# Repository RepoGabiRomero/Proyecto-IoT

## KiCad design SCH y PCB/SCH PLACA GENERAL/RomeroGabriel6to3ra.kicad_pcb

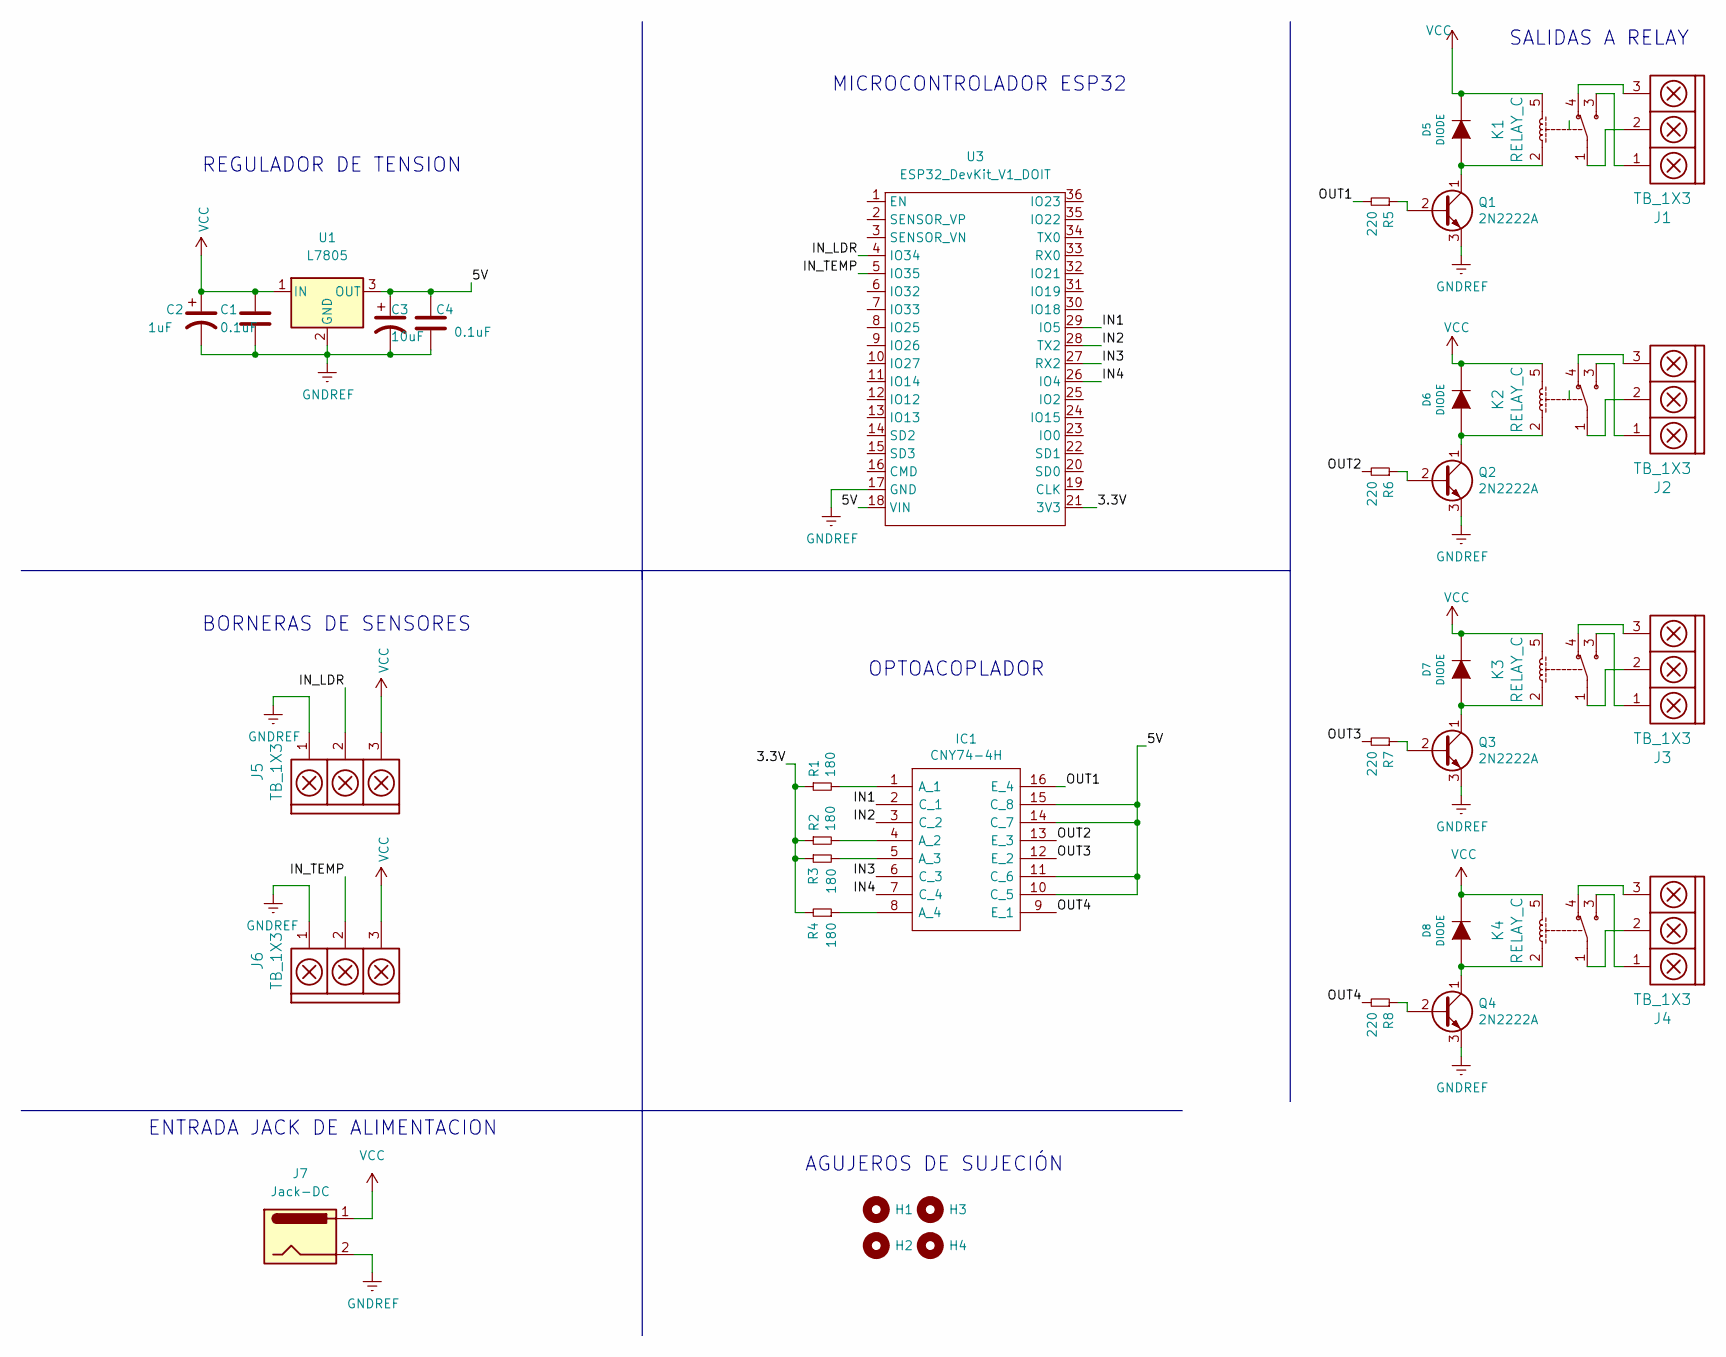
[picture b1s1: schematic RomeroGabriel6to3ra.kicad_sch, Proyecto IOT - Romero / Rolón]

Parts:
C1, C4: 0.1uF; CAP_0.1
C2: 1uF; CAP_ELEC_5x11mm
C3: 10uF; CAP_ELEC_5x11mm
D5, D6, D7, D8: DIODE; DO-41
H1, H2, H3, H4: Mounting_Hole; MountingHole_3mm
IC1: CNY74-4H; DIP_16-300; Manufacturer_Part_Number CNY74-4H; Mouser Part Number 782-CNY74-4H
J1, J2, J3, J4, J5, J6: TB_1X3; BORNERA3
J7: Jack-DC; BarrelJack_Wuerth_6941xx301002
K1, K2, K3, K4: RELAY_C; Relay_C
Q1, Q2, Q3, Q4: 2N2222A; to92
R1, R2, R3, R4: 180; RES0.3
R5, R6, R7, R8: 220; RES0.3
U1: L7805; TO-220
U3: ESP32_DevKit_V1_DOIT; ESP32_DEVKITC

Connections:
/3.3V: R1.1, R2.1, R3.1, R4.2, U3.21 (3V3)
/5V: C3.1, C4.1, IC1.10 (C_5), IC1.11 (C_6), IC1.14 (C_7), IC1.15 (C_8), U1.3 (OUT), U3.18 (VIN)
/IN1: IC1.2 (C_1), U3.29 (IO5)
/IN2: IC1.3 (C_2), U3.28 (TX2)
/IN3: IC1.6 (C_3), U3.27 (RX2)
/IN4: IC1.7 (C_4), U3.26 (IO4)
/IN_LDR: J5.2, U3.4 (IO34)
/IN_TEMP: J6.2, U3.5 (IO35)
/OUT1: IC1.16 (E_4), R5.2
/OUT2: IC1.13 (E_3), R6.2
/OUT3: IC1.12 (E_2), R7.2
/OUT4: IC1.9 (E_1), R8.2
GNDREF: C1.2, C2.2, C3.2, C4.2, J5.1, J6.1, J7.2, Q1.3 (E), Q2.3 (E), Q3.3 (E), Q4.3 (E), U1.2 (GND), U3.17 (GND)
unnamed: D5.1 (A), K1.2, Q1.1 (C)
unnamed: D6.1 (A), K2.2, Q2.1 (C)
unnamed: D7.1 (A), K3.2, Q3.1 (C)
unnamed: D8.1 (A), K4.2, Q4.1 (C)
unnamed: IC1.1 (A_1), R1.2
unnamed: IC1.4 (A_2), R2.2
unnamed: IC1.5 (A_3), R3.2
unnamed: IC1.8 (A_4), R4.1
unnamed: J1.1, K1.3
unnamed: J1.2, K1.1
unnamed: J1.3, K1.4
unnamed: J2.1, K2.3
unnamed: J2.2, K2.1
unnamed: J2.3, K2.4
unnamed: J3.1, K3.3
unnamed: J3.2, K3.1
unnamed: J3.3, K3.4
unnamed: J4.1, K4.3
unnamed: J4.2, K4.1
unnamed: J4.3, K4.4
unnamed: Q1.2 (B), R5.1
unnamed: Q2.2 (B), R6.1
unnamed: Q3.2 (B), R7.1
unnamed: Q4.2 (B), R8.1
VCC: C1.1, C2.1, D5.2 (K), D6.2 (K), D7.2 (K), D8.2 (K), J5.3, J6.3, J7.1, K1.5, K2.5, K3.5, K4.5, U1.1 (IN)

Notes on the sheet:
ENTRADA JACK DE ALIMENTACION
MICROCONTROLADOR ESP32
BORNERAS DE SENSORES
AGUJEROS DE SUJECIÓN
SALIDAS A RELAY
REGULADOR DE TENSION
OPTOACOPLADOR

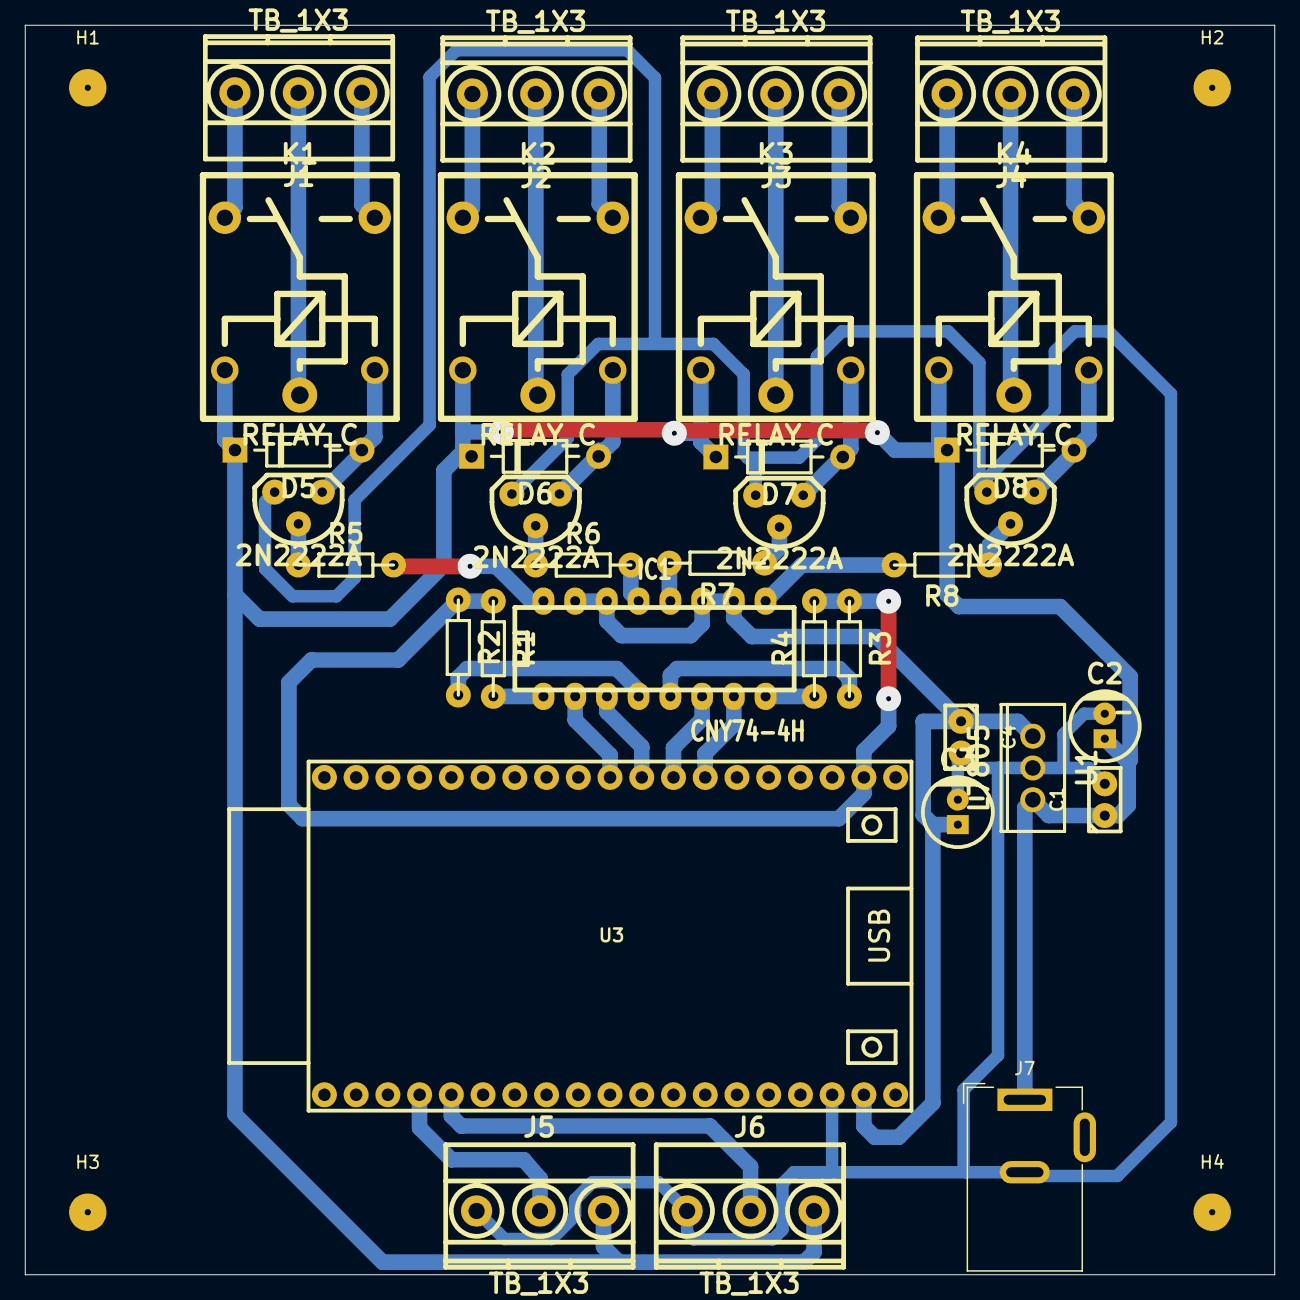
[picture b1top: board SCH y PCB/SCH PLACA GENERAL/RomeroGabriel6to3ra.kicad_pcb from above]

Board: 2 copper layers, 100.0 x 100.0 mm, 38 parts (0 on the bottom side), 38 nets.

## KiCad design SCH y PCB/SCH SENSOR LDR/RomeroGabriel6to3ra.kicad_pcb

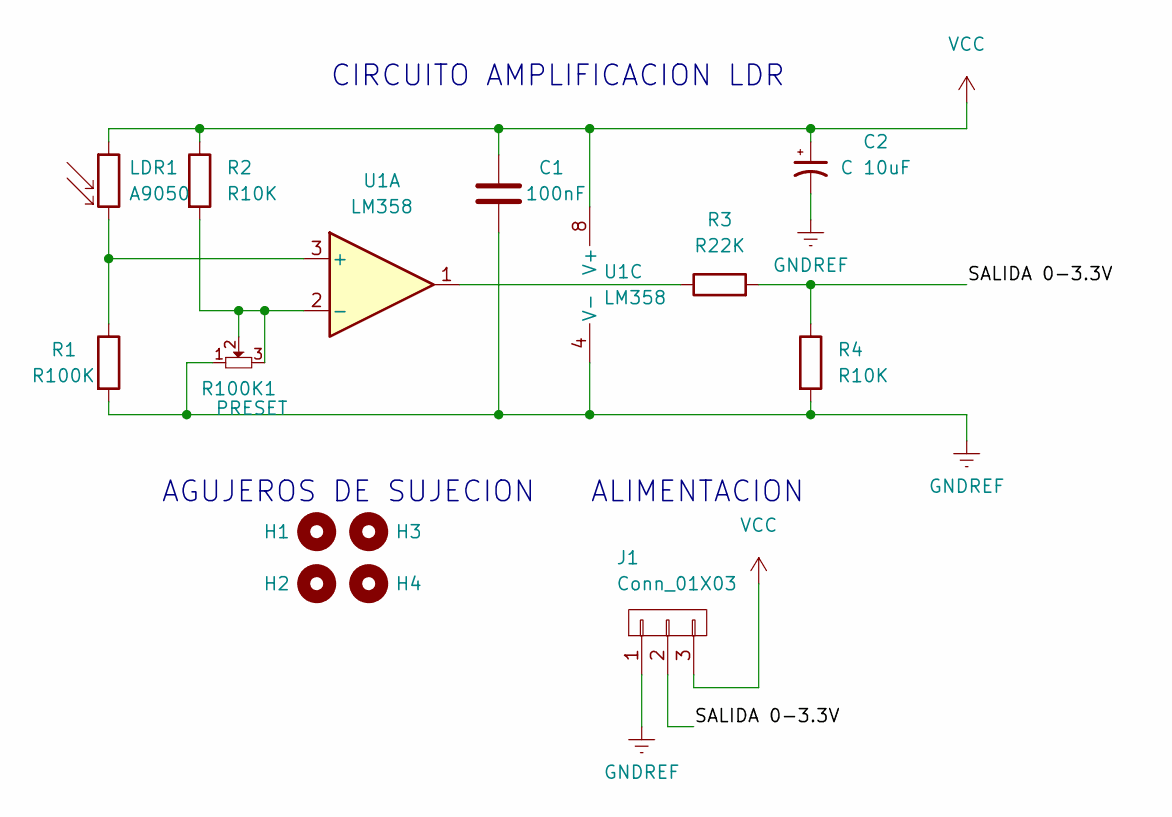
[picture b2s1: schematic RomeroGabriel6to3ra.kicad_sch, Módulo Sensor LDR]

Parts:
C1: 100nF; CAP_0.1
C2: C 10uF; CAP_ELEC_5x11mm
H1, H2, H3, H4: Mounting_Hole; MountingHole_3mm
J1: Conn_01X03; Pin_Header_3
LDR1: A9050; R_LDR_5.0x4.1mm_P3mm_Vertical
R1: R100K; RES0.3
R2, R4: R10K; RES0.3
R3: R22K; RES0.3
R100K1: PRESET; to92
U1: LM358; DIP-8

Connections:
/SALIDA 0-3.3V: J1.2, R3.2, R4.1
GNDREF: C1.1, C2.2, J1.1, R1.2, R4.2, R100K1.1, U1.4 (V-)
unnamed: LDR1.2, R1.1, U1.3 (+)
unnamed: R3.1, U1.1
unnamed: R2.2, R100K1.2, R100K1.3, U1.2 (-)
VCC: C1.2, C2.1, J1.3, LDR1.1, R2.1, U1.8 (V+)

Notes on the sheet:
ALIMENTACION
CIRCUITO AMPLIFICACION LDR
AGUJEROS DE SUJECION

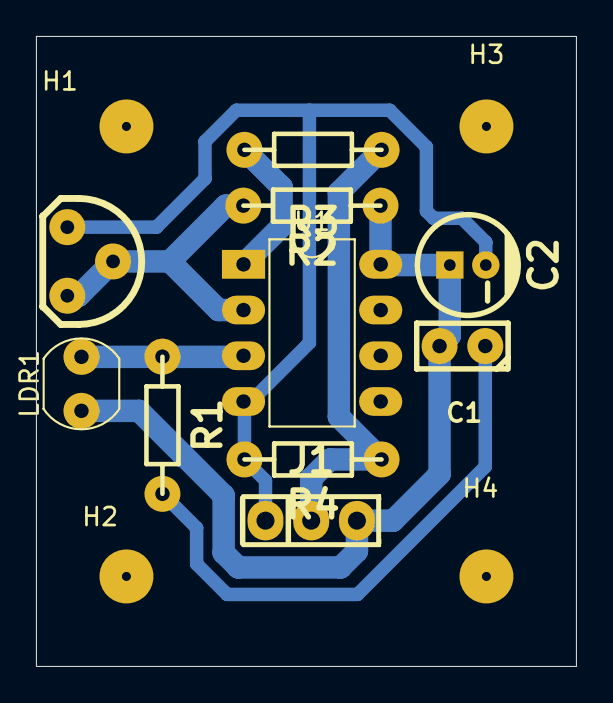
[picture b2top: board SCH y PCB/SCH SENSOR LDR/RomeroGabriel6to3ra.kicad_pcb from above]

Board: 2 copper layers, 30.0 x 35.0 mm, 14 parts (0 on the bottom side), 6 nets.

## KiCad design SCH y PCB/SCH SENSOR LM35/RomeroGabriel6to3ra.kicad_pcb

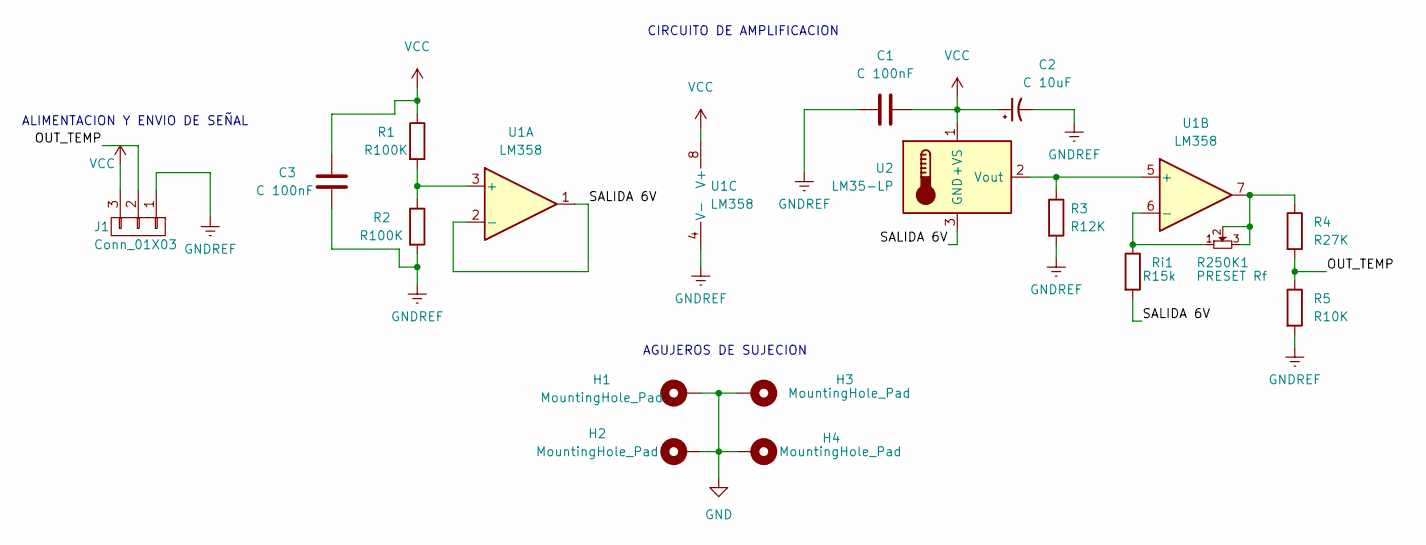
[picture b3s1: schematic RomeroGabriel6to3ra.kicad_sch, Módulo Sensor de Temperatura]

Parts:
C1, C3: C 100nF; CAP_0.1
C2: C 10uF; CAP_ELEC_5x11mm
H1, H2, H3, H4: MountingHole_Pad; MountingHole_3mm_Pad
J1: Conn_01X03; Cable_3_1,5mm
R1, R2: R100K; RES0.3
R3: R12K; RES0.3
R4: R27K; RES0.3
R5: R10K; RES0.3
R250K1: PRESET Rf; Pin_Header_3
Ri1: R15k; RES0.3
U1: LM358; DIP-8
U2: LM35-LP; Pin_Header_3

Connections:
/OUT_TEMP: J1.2, R4.2, R5.1
/SALIDA 6V: Ri1.2, U1.1, U1.2 (-), U2.3 (GND)
GND: H1.1, H2.1, H3.1, H4.1
GNDREF: C1.1, C2.2, C3.2, J1.1, R2.2, R3.2, R5.2, U1.4 (V-)
unnamed: R1.2, R2.1, U1.3 (+)
unnamed: R3.1, U1.5 (+), U2.2 (Vout)
unnamed: R250K1.1, Ri1.1, U1.6 (-)
unnamed: R4.1, R250K1.2, R250K1.3, U1.7
VCC: C1.2, C2.1, C3.1, J1.3, R1.1, U1.8 (V+), U2.1 (+VS)

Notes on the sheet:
ALIMENTACION Y ENVIO DE SEÑAL
AGUJEROS DE SUJECION
CIRCUITO DE AMPLIFICACION

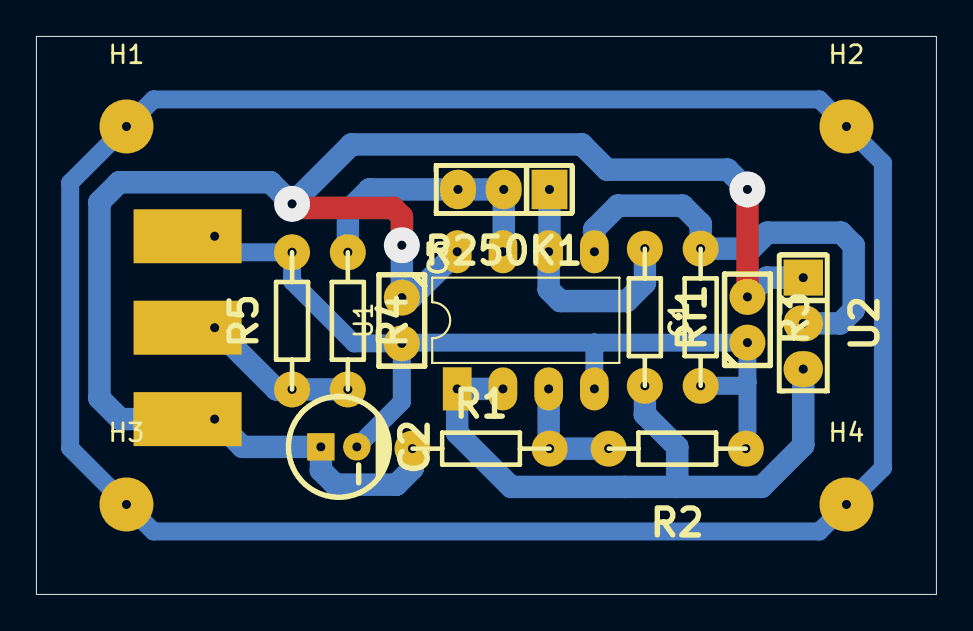
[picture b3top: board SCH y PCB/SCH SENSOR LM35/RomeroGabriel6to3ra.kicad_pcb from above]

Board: 2 copper layers, 50.0 x 31.0 mm, 17 parts (0 on the bottom side), 9 nets.

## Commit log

2022-11-24 SCH y PCB del Proyecto
2022-11-24 Programacion aplicada al proyecto
